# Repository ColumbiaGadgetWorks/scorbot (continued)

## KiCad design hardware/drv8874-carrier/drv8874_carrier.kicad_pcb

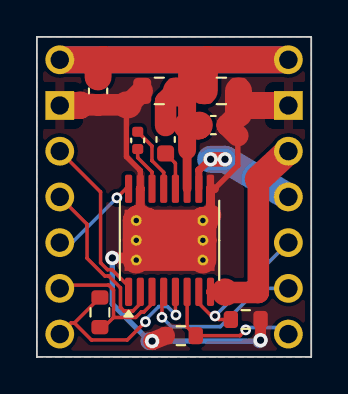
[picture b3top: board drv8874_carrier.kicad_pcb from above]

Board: 2 copper layers, 15.2 x 17.8 mm, 12 parts (0 on the bottom side), 15 nets.

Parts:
C1, C2: 10uF 25V; C_0805_2012Metric
C3, C4, C6: 100nF 50V; C_0603_1608Metric
C5: 22nF 50V; C_0402_1005Metric
J1, J2: 1x7 0.1in pins (hand-soldered); PinHeader_1x07_P2.54mm_Vertical
R2: 10k; R_0603_1608Metric
R3: 2.4k 1%; R_0603_1608Metric
R4: 20k; R_0603_1608Metric
U1: DRV8874PWPR; HTSSOP-16-1EP_4.4x5mm_P0.65mm_EP3.4x5mm_Mask2.46x2.31mm

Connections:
CPH: C5.2, U1.13
CPL: C5.1, U1.14
CS: J2.7, R3.2, U1.6
EN: J1.3, U1.1
FAULT: J2.6, U1.4
GND: C1.1, C2.2, C3.2, C4.1, J1.2, J2.2, R3.1, R4.2, U1.9, U1.15, U1.17
IMODE: J2.5, R4.1, U1.7
OUT1: J2.3, U1.8
OUT2: J2.4, U1.10
PH: J1.4, U1.2
PMODE: J1.5, U1.16
SLEEP: J1.6, R2.1, U1.3
VCP: C6.1, U1.12
VM: C1.2, C2.1, C3.1, C4.2, C6.2, J1.1, J2.1, U1.11
VREF: J1.7, R2.2, U1.5

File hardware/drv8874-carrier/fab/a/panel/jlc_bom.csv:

Comment,Designator,Footprint,LCSC Part #
10uF 25V,"C1_1,C1_2,C1_3,C1_4,C1_5,C1_6,C2_1,C2_2,C2_3,C2_4,C2_5,C2_6",C_0805_2012Metric,C15850
100nF 50V,"C3_1,C3_2,C3_3,C3_4,C3_5,C3_6,C4_1,C4_2,C4_3,C4_4,C4_5,C4_6,C6_1,C6_2,C6_3,C6_4,C6_5,C6_6",C_0603_1608Metric,C14663
2.4k 1%,"R3_1,R3_2,R3_3,R3_4,R3_5,R3_6",R_0603_1608Metric,C22940
10k,"R2_1,R2_2,R2_3,R2_4,R2_5,R2_6",R_0603_1608Metric,C25804
20k,"R4_1,R4_2,R4_3,R4_4,R4_5,R4_6",R_0603_1608Metric,C4184
22nF 50V,"C5_1,C5_2,C5_3,C5_4,C5_5,C5_6",C_0402_1005Metric,C1532
DRV8874PWPR,"U1_1,U1_2,U1_3,U1_4,U1_5,U1_6",HTSSOP-16-1EP_4.4x5mm_P0.65mm_EP3.4x5mm_Mask2.46x2.31mm,C1855818

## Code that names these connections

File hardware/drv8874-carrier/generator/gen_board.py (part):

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
# Carrier pins, top view, top to bottom (Pololu's labelled pinout).
LEFT = ["VM", "GND", "EN", "PH", "PMODE", "SLEEP", "VREF"]      # x = 1.27
RIGHT = ["VM", "GND", "OUT1", "OUT2", "IMODE", "FAULT", "CS"]   # x = 13.97, top pin is VIN (tied to VM)
RIGHT_LABELS = ["VIN", "GND", "OUT1", "OUT2", "IMODE", "FLT", "CS"]
LEFT_LABELS = ["VM", "GND", "EN", "PH", "PMODE", "SLP", "VREF"]

# DRV8874 (HTSSOP-16, PWP) pin -> net
DRV = {1: "EN", 2: "PH", 3: "SLEEP", 4: "FAULT", 5: "VREF", 6: "CS", 7: "IMODE", 8: "OUT1",
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           (B, 1.2, [(1.27, 1.27), (13.97, 1.27)]),
           (F, 1.0, [(VMX, 1.27), (VMX, 6.3)]),               # down to pin 11
           (F, 0.4, [(VMX, 6.3), (VMX, TY)])],
    "OUT2": [(F, 0.4, [(O2X, TY), (O2X, 7.4), (O2X + 0.655, 6.8)]),   # pin 10 up, two vias, B.Cu to J2
             (F, 0.8, [(O2X + 0.655, 6.8), (O2X + 1.455, 6.8)]),
             (B, 1.2, [(O2X + 0.655, 6.8), (O2X + 1.455, 6.8), (13.97, 8.89)])],
    "OUT1": [(F, 0.4, [(O1X, BY), (O1X + 0.8, BY)]),                 # pin 8 right, up the right side
             (F, 1.2, [(O1X + 0.8, 14.2), (12.3, 14.2), (12.3, 7.9), (13.97, 6.35)])],
    "GND": [(F, 0.4, [(top_x(9), TY), (top_x(9), 9.9)]),            # pins 9 and 15 into the thermal land
            (F, 0.4, [(top_x(15), TY), (top_x(15), 9.9)]),
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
